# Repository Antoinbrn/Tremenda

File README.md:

# ESP32 MP3 Player

A Spotify-like MP3 player built on ESP32-WROOM-32 with Bluetooth A2DP audio output, OLED display, and SD card storage.

## Features

- **Bluetooth A2DP Sink** - Connect to wireless earbuds/headphones
- **SD Card Support** - MP3, WAV, FLAC, M4A, AAC, OGG playback
- **Spotify-like UI** - Now Playing, Library, Search, Settings on 128x64 OLED
- **4-Button Navigation** - Up, Down, Left, Right with long-press actions
- **Potentiometer Volume** - Smooth analog volume control
- **Folder-based Playlists** - Each folder = one playlist
- **Shuffle Mode** - Fisher-Yates shuffle
- **Real-time Search** - Filter by filename
- **Battery Monitoring** - Voltage display with low-battery warning
- **Deep Sleep** - 10 min pause timeout for 2+ year battery life

## Hardware Requirements

| Component | Specification | Pins |
|-----------|--------------|------|
| ESP32-WROOM-32 | Dev board with USB | All |
| 0.96" OLED | SSD1306 128x64 I2C | GPIO21 (SDA), GPIO22 (SCL) |
| MicroSD Module | SPI interface | GPIO5 (CS), GPIO18 (SCK), GPIO19 (MISO), GPIO23 (MOSI) |
| 10kΩ Potentiometer | Volume control | GPIO34 (ADC1_CH6) |
| 4x Tactile Buttons | 6x6mm 4-pin | GPIO25, 26, 32, 33 |
| LiPo Battery | 3.7V 2000mAh+ | - |
| TP4056 Module | LiPo charger + protection | - |
| 3.3V LDO | AMS1117-3.3 | - |

See [hardware/parts_list.csv](hardware/parts_list.csv) for complete parts list with links.

## Wiring

See [hardware/wiring_guide.md](hardware/wiring_guide.md) for detailed wiring diagram and instructions.

### Pinout Summary

```
ESP32 Pin -> Function
---------   --------
GPIO21      OLED SDA
GPIO22      OLED SCL
GPIO5       SD Card CS
GPIO18      SD Card SCK
GPIO19      SD Card MISO
GPIO23      SD Card MOSI
GPIO34      Potentiometer (Volume)
GPIO35      Battery Monitor (via divider)
GPIO25      Button LEFT
GPIO26      Button RIGHT
GPIO32      Button UP
GPIO33      Button DOWN
GPIO2       Status LED
```

## Software Setup

### Prerequisites

- PlatformIO Core or PlatformIO IDE extension
- ESP32 board support (`pio platform install espressif32`)

### Build and Flash

```bash
cd esp32_mp3_player
pio run -t upload
```

### Monitor Serial Output

```bash
pio device monitor -b 115200
```

### Run Tests

```bash
pio test -e esp32dev_test
```

## SD Card Preparation

1. Format SD card as FAT32
2. Create folder structure:
   ```
   /Music/
     /Rock/
       song1.mp3
       song2.mp3
     /Pop/
       song3.mp3
     /Jazz/
       song4.flac
   /Podcasts/
     episode1.mp3
   ```
3. Insert into SD card module

## First Boot

1. Power on the device
2. Put Bluetooth earbuds in pairing mode
3. Device will auto-connect to "ESP32_MP3_Player"
4. Use buttons to navigate

## Controls

| Button | Now Playing | Library/Playlist | Search | Settings |
|--------|-------------|------------------|--------|----------|
| **Right** | Play/Pause | Enter/Select | Select key | Toggle |
| **Left** | Back to Library | Back | Backspace/Back | Back |
| **Up** | Previous Track | Navigate Up | Keyboard Up | Navigate Up |
| **Down** | Next Track | Navigate Down | Keyboard Down/Results | Navigate Down |
| **Long Left** | Toggle Shuffle | - | - | - |
| **Potentiometer** | Volume | Volume | Volume | Volume |

## Screens

1. **Now Playing** - Album art placeholder, track info, progress bar, volume
2. **Library** - "All Songs" + folder playlists
3. **Playlist** - Track list with playing indicator
4. **Search** - Virtual keyboard + real-time results
5. **Settings** - Shuffle, Auto-play, Brightness, Factory Reset

## Project Structure

```
esp32_mp3_player/
├── platformio.ini          # PlatformIO config
├── custom_partitions.csv   # Partition table (OTA + SPIFFS)
├── src/
│   ├── main.cpp           # Entry point, task management
│   ├── config.h           # Pin definitions, constants
│   ├── audio/             # Audio playback, Bluetooth A2DP, SD card
│   ├── ui/                # OLED UI, screens, components
│   ├── input/             # Buttons, potentiometer
│   ├── storage/           # File indexing, playlist management
│   └── utils/             # String, time, memory utilities
├── test/                  # Unit tests (Unity)
├── hardware/              # Wiring guide, parts list, schematics
├── data/                  # SPIFFS files (fonts, images)
└── docs/                  # API reference, troubleshooting
```

## Configuration

Edit `src/config.h` to customize:
- Pin assignments
- Audio buffer sizes
- UI refresh rates
- Button timing
- Power management thresholds

## Power Management

- **Active**: ~150mA (Bluetooth + OLED + SD)
- **Dimmed**: ~100mA (OLED dimmed after 30s)
- **Deep Sleep**: ~10µA (after 10 min paused)
- **Battery Life**: ~20+ hours continuous, 2+ years with sleep

## Troubleshooting

| Issue | Solution |
|-------|----------|
| No sound | Check Bluetooth connection, volume potentiometer |
| SD card not detected | Check wiring, format FAT32, try different card |
| OLED not showing | Check I2C connections, try 0x3D address |
| Buttons not working | Check pull-up resistors, pin assignments |
| Short battery life | Check for shorts, verify deep sleep works |

See [docs/troubleshooting.md](docs/troubleshooting.md) for more details.

## License

MIT License - Feel free to use and modify.

## Credits

- [ESP32-audioI2S](https://github.com/pschatzmann/ESP32-audioI2S) by pschatzmann
- [Adafruit SSD1306](https://github.com/adafruit/Adafruit_SSD1306)
- [ArduinoJson](https://github.com/bblanchon/ArduinoJson)

---

**Built with PlatformIO and ESP32 Arduino Core**

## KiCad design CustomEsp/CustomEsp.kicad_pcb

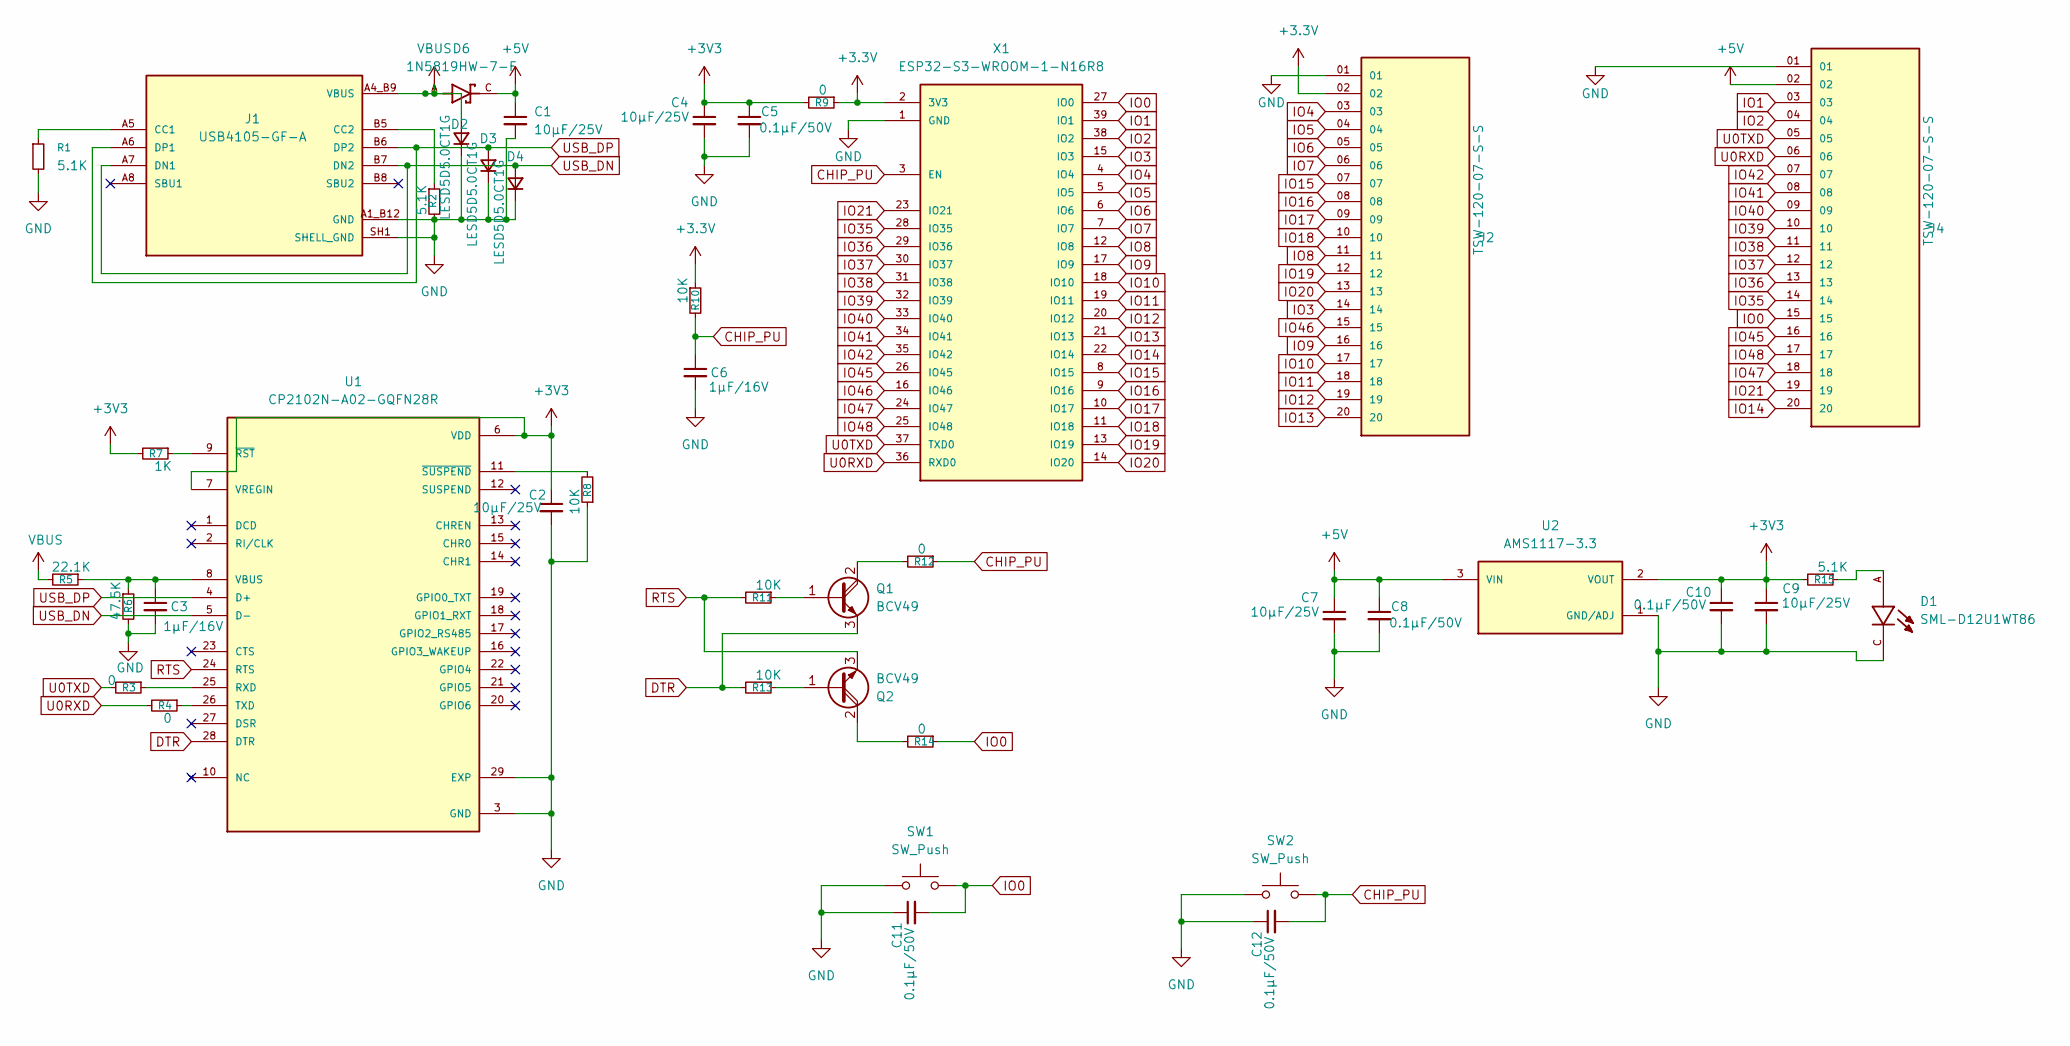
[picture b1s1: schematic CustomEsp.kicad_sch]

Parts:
C1, C2, C4, C7, C9: 10µF/25V; CAPC3216X110N
C3, C6: 1µF/16V; CAPC1608X90N
C5, C8, C10, C11, C12: 0.1µF/50V; CAPC1608X92N
D1: SML-D12U1WT86; LED_SML-D12U1WT86; PARTREV 007
D2, D3, D4: LESD5D5.0CT1G; TVS_LESD5D5.0CT1G
D6: 1N5819HW-7-F; SOD3715X145N; PARTREV 18-2
J1: USB4105-GF-A; GCT_USB4105-GF-A; PARTREV B4
J2, J4: TSW-120-07-S-S; SAMTEC_TSW-120-07-S-S; PARTREV R
Q1, Q2: BCV49; MMBT4401_R1_00001
R1, R2, R15: 5.1K; RES_ERJU06F5101V
R3, R4, R9, R12, R14: 0; RES_ERJU030R00V
R5: 22.1K; RES_ERA8AEB2212V
R6: 47.5K; RES_ERJPA3D4752V
R7: 1K; RES_ERJU06J102V
R8, R10, R11, R13: 10K; RES_ERA2APB103X
SW1, SW2: SW_Push; SWITCH_43SMTR92LFS
U1: CP2102N-A02-GQFN28R; IC_CP2102N-A02-GQFN28R; PARTREV 1.5
U2: AMS1117-3.3; SOT229P700X180-4N; PARTREV N/A
X1: ESP32-S3-WROOM-1-N16R8; ESP32S3WROOM1N8R2; MANUFACTURER_PART_NUMBER ESP32-S3-WROOM-1-N16R8

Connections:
+3.3V: J2.02, R9.1, R10.1, X1.2 (3V3)
+3V3: C2.1, C4.1, C5.1, C9.1, C10.1, R7.2, R9.2, R15.2, U1.6 (VDD), U1.7 (VREGIN), U2.2 (VOUT)
+5V: C1.1, C7.1, C8.1, D6.C, J4.02, U2.3 (VIN)
CHIP_PU: C6.1, C12.2, R10.2, R12.1, SW2.2, X1.3 (EN)
DTR: Q1.3 (E), R13.2, U1.28 (DTR)
GND: C1.2, C2.2, C3.2, C4.2, C5.2, C6.2, C7.2, C8.2, C9.2, C10.2, C11.1, C12.1, D1.C, D2.1 (K), D3.1 (K), D4.1 (K), J1.A1_B12 (GND), J1.B1_A12 (GND), J1.SH1 (SHELL_GND), J1.SH2 (SHELL_GND), J1.SH3 (SHELL_GND), J1.SH4 (SHELL_GND), J2.01, J4.01, R1.2, R2.2, R6.2, R8.1, SW1.1, SW2.1, U1.3 (GND), U1.29 (EXP), U2.1 (GND/ADJ), X1.1 (GND), X1.40 (GND), X1.41 (GND), X1.42 (GND), X1.43 (GND), X1.44 (GND), X1.45 (GND), X1.46 (GND), X1.47 (GND), X1.48 (GND), X1.49 (GND)
IO0: C11.2, J4.15, R14.1, SW1.2, X1.27 (IO0)
IO1: J4.03, X1.39 (IO1)
IO2: J4.04, X1.38 (IO2)
IO3: J2.14, X1.15 (IO3)
IO4: J2.03, X1.4 (IO4)
IO5: J2.04, X1.5 (IO5)
IO6: J2.05, X1.6 (IO6)
IO7: J2.06, X1.7 (IO7)
IO8: J2.11, X1.12 (IO8)
IO9: J2.16, X1.17 (IO9)
IO10: J2.17, X1.18 (IO10)
IO11: J2.18, X1.19 (IO11)
IO12: J2.19, X1.20 (IO12)
IO13: J2.20, X1.21 (IO13)
IO14: J4.20, X1.22 (IO14)
IO15: J2.07, X1.8 (IO15)
IO16: J2.08, X1.9 (IO16)
IO17: J2.09, X1.10 (IO17)
IO18: J2.10, X1.11 (IO18)
IO19: J2.12, X1.13 (IO19)
IO20: J2.13, X1.14 (IO20)
IO21: J4.19, X1.23 (IO21)
IO35: J4.14, X1.28 (IO35)
IO36: J4.13, X1.29 (IO36)
IO37: J4.12, X1.30 (IO37)
IO38: J4.11, X1.31 (IO38)
IO39: J4.10, X1.32 (IO39)
IO40: J4.09, X1.33 (IO40)
IO41: J4.08, X1.34 (IO41)
IO42: J4.07, X1.35 (IO42)
IO45: J4.16, X1.26 (IO45)
IO46: J2.15, X1.16 (IO46)
IO47: J4.18, X1.24 (IO47)
IO48: J4.17, X1.25 (IO48)
unnamed: D1.A, R15.1
unnamed: J1.A5 (CC1), R1.1
unnamed: J1.B5 (CC2), R2.1
unnamed: Q1.1 (B), R11.1
unnamed: Q1.2 (C), R12.2
unnamed: Q2.1 (B), R13.1
unnamed: Q2.2 (C), R14.2
unnamed: R3.1, U1.25 (RXD)
unnamed: R4.1, U1.26 (TXD)
unnamed: C3.1, R5.1, R6.1, U1.8 (VBUS)
unnamed: R7.1, U1.9 (~RST)
unnamed: R8.2, U1.11 (~SUSPEND)
RTS: Q2.3 (E), R11.2, U1.24 (RTS)
U0RXD: J4.06, R4.2, X1.36 (RXD0)
U0TXD: J4.05, R3.2, X1.37 (TXD0)
USB_DN: D4.2 (A), J1.A7 (DN1), J1.B7 (DN2), U1.5 (D-)
USB_DP: D3.2 (A), J1.A6 (DP1), J1.B6 (DP2), U1.4 (D+)
VBUS: D2.2 (A), D6.A, J1.A4_B9 (VBUS), J1.B4_A9 (VBUS), R5.2

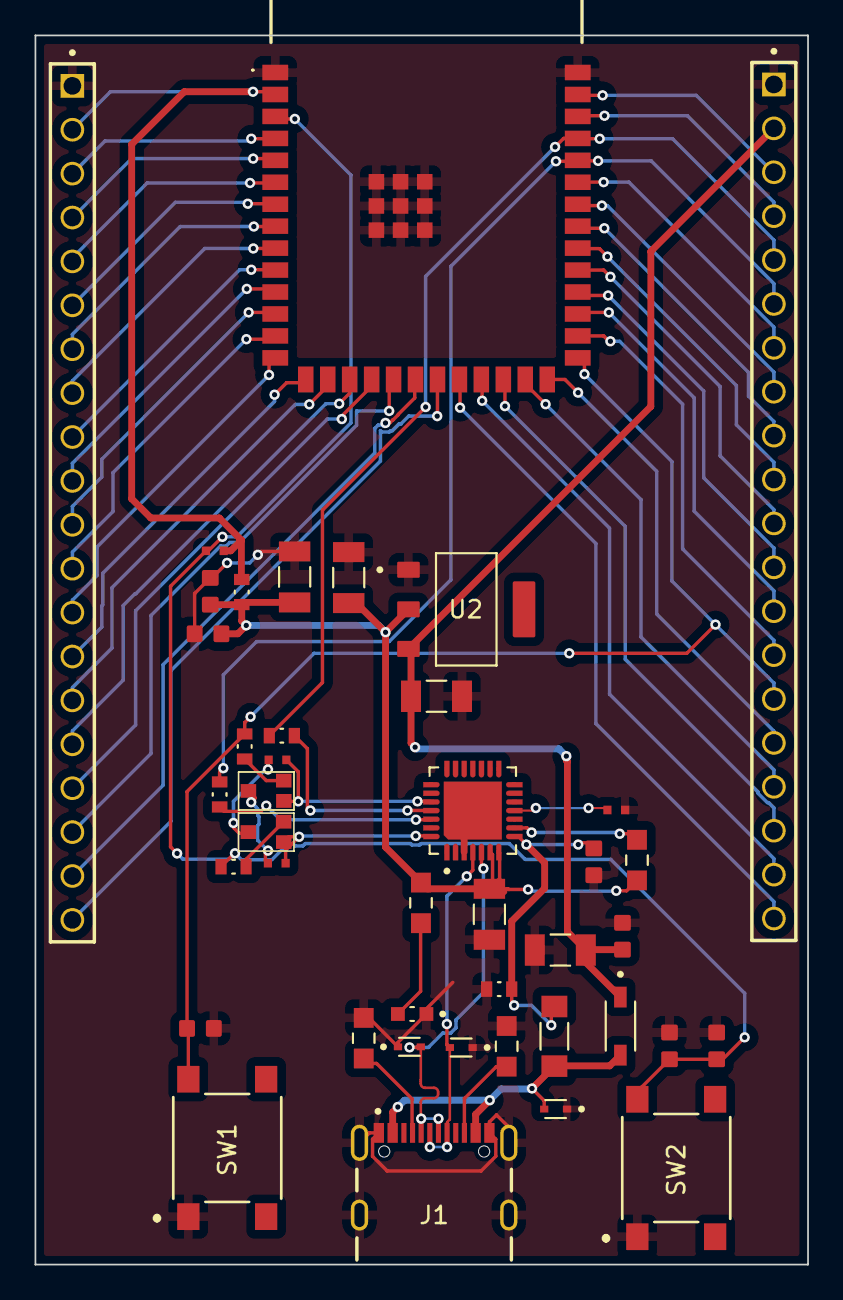
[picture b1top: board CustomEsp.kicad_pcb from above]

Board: 4 copper layers, 44.7 x 71.1 mm, 42 parts (0 on the bottom side), 58 nets.

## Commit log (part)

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2026-06-28 Added essential files for the code
2026-06-28 Fixed corrupted files
